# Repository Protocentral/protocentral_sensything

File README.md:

ProtoCentral Sensything
=======================================================

### Support us now on Crowd Supply at: https://www.crowdsupply.com/protocentral/sensything

Sensything is an ESP32-based IoT device that has multiple sensor interfaces to read from and send data from both analog and digital sensors.

## Information will be added constantly, keep checking this page for more.

License Information
===================

This product is open source! Both, our hardware and software are open source and licensed under the following licenses:

Hardware
---------

**All hardware is released under [Creative Commons Share-alike 4.0 International](http://creativecommons.org/licenses/by-sa/4.0/).**

You are free to:

* Share — copy and redistribute the material in any medium or format
* Adapt — remix, transform, and build upon the material for any purpose, even commercially.
The licensor cannot revoke these freedoms as long as you follow the license terms.

Under the following terms:

* Attribution — You must give appropriate credit, provide a link to the license, and indicate if changes were made. You may do so in any reasonable manner, but not in any way that suggests the licensor endorses you or your use.
* ShareAlike — If you remix, transform, or build upon the material, you must distribute your contributions under the same license as the original.

Software
--------

**All software is released under the MIT License(http://opensource.org/licenses/MIT).**

THE SOFTWARE IS PROVIDED "AS IS", WITHOUT WARRANTY OF ANY KIND, EXPRESS OR IMPLIED, INCLUDING BUT NOT LIMITED TO THE WARRANTIES OF MERCHANTABILITY, FITNESS FOR A PARTICULAR PURPOSE AND NONINFRINGEMENT. IN NO EVENT SHALL THE AUTHORS OR COPYRIGHT HOLDERS BE LIABLE FOR ANY CLAIM, DAMAGES OR OTHER LIABILITY, WHETHER IN AN ACTION OF CONTRACT, TORT OR OTHERWISE, ARISING FROM, OUT OF OR IN CONNECTION WITH THE SOFTWARE OR THE USE OR OTHER DEALINGS IN THE SOFTWARE.

Please check [*LICENSE.md*](LICENSE.md) for detailed license descriptions.

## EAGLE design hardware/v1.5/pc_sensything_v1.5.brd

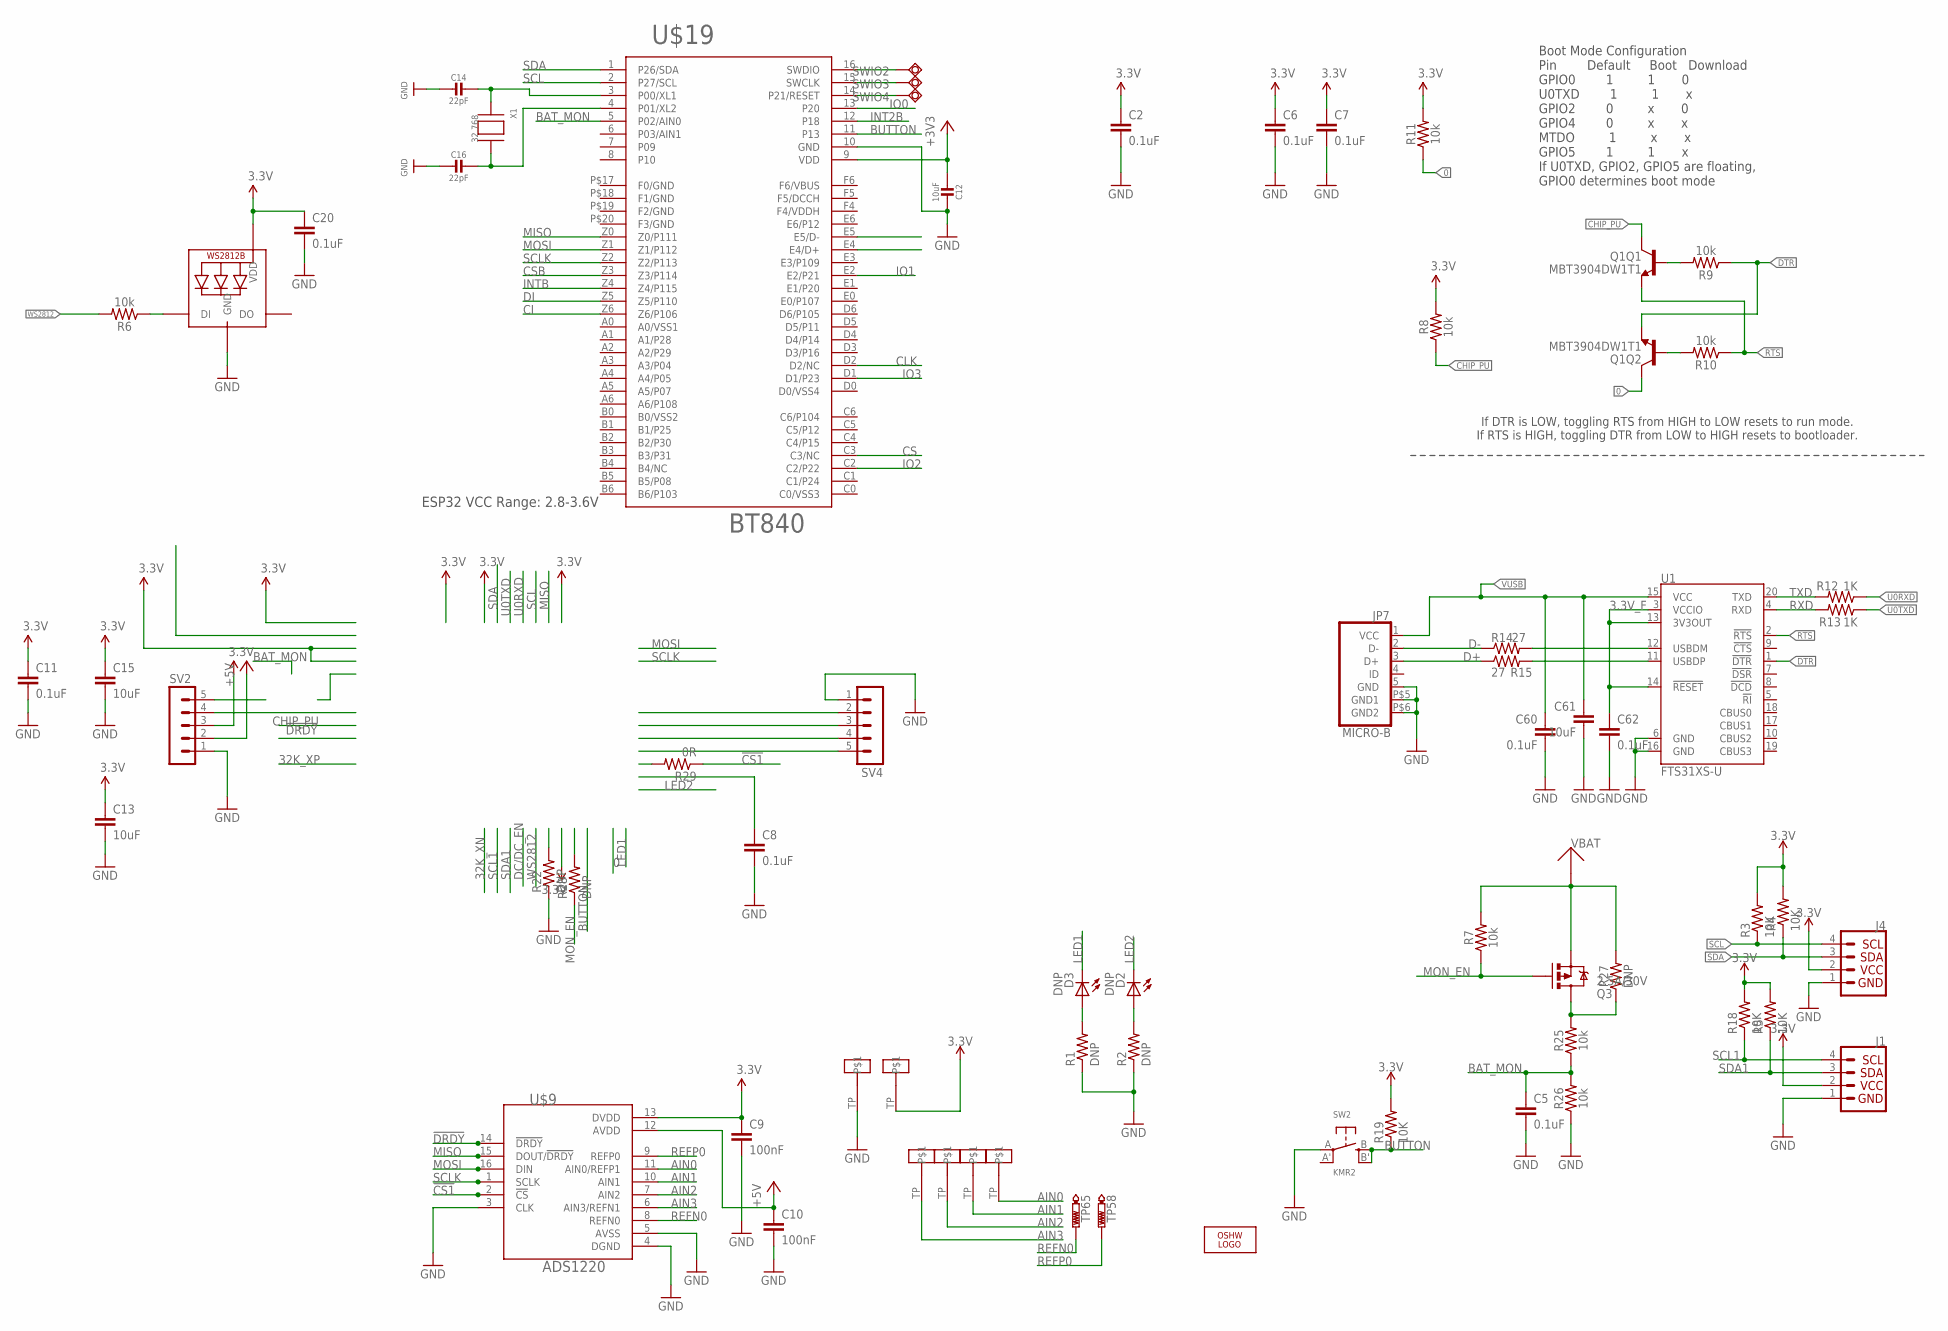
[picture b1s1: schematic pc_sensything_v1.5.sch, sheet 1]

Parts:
C2, C5, C6, C7, C8, C11: 0.1uF; 0402
C9, C10: 100nF; C0805
C12: 10uF; _0402
C13, C15: 10uF; 0603
C14, C16: 22pF; _0402
C20: 0.1uF; 0603
C60, C62: 0.1uF; C0402
C61: 10uF; C0805
D2, D3: DNP; CHIPLED_0603
J1, J4: QWIIC_CONNECTORJS-1MM; 1X04_1MM_RA
JP7: MICRO-B
LED1: WS2812B5050; WS2812B
LOGO3: OSHW_LOGO_FILLX0200-NT; OSHW_FILLX200_NOTEXT
Q1: MBT3904DW1T1; SC70-6
Q3: 2.5A/30V; SOT23-3
R1, R2, R22, R28: DNP; R0402
R3, R4, R5, R18, R19: 10K; R0402
R6, R7, R8, R9, R10, R11, R25, R26: 10k; 0603
R12, R13: 1K; R0402
R14, R15: 27; R0402
R27: DNP; 0603
R29: 0R; R0402
SV2, SV4: MA05-1
SW2: KMR2; BTN_KMR2_4.6X2.8
SWIO2, SWIO3, SWIO4: TPSQTP11R; TP11R
TP58, TP65: PTR1PAD1-13; P1-13
U1: FTS31XS-U; SSOP20_L
U$3, U$7, U$8, U$11, U$12, U$14: SENSYTHING_CON
U$9: ADS1220; TSSOP-16
U$19: BT840
X1: 32.768; XTAL3215

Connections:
0: Q1.6 (C), R11.1
3.3V: C2.1, C6.1, C7.1, C9.1, C11.1, C13.1, C15.1, C20.1, J1.2, J4.2, LED1.1-VDD (VDD), R3.2, R4.2, R5.2, R8.2, R11.2, R18.2, R19.2, SV2.3, U$9.13 (DVDD), U$14.TP; also elsewhere on the board
3.3V_F: C62.1, U1.3 (VCCIO), U1.13 (3V3OUT), U1.14 (!RESET)
!CS1: R29.1, U$9.2 (!CS)
!DRDY: U$9.14 (!DRDY)
+3V3: C12.1, U$19.9 (VDD)
+5V: C10.1, SV2.2, U$9.12 (AVDD); also elsewhere on the board
AIN0: U$9.11 (AIN0/REFP1), U$11.TP
AIN1: U$8.TP, U$9.10 (AIN1)
AIN2: U$7.TP, U$9.7 (AIN2)
AIN3: U$3.TP, U$9.6 (AIN3/REFN1)
BAT_MON: C5.1, R25.1, R26.2, U$19.5 (P02/AIN0)
BUTTON: R19.1, SW2.B (S), SW2.B' (S1), U$19.11 (P13)
CHIP_PU: Q1.3 (C), R8.1
CI: U$19.Z6 (Z6/P106)
CLK: U$19.D2 (D2/NC)
CS: U$19.C3 (C3/NC)
CSB: U$19.Z3 (Z3/P114)
D+: JP7.3 (D+), R15.1
D-: JP7.2 (D-), R14.1
DI: U$19.Z5 (Z5/P110)
DTR: Q1.1 (E), R9.1, U1.1 (!DTR)
GND: C2.2, C5.2, C6.2, C7.2, C8.2, C9.2, C10.2, C11.2, C12.2, C13.2, C14.2, C15.2, C16.2, C20.2, C60.2, C61.2, C62.2, J1.1, J4.1, JP7.5 (GND), JP7.P$5 (GND1), JP7.P$6 (GND2), LED1.3-GND (GND), R1.1, R2.1, R22.1, R26.1, SV2.1, SV4.1, SW2.A, U1.6 (GND), U1.16 (GND), U$9.3 (CLK), U$9.4 (DGND), U$9.5 (AVSS), U$12.TP, U$19.10 (GND); also elsewhere on the board
INT2B: U$19.12 (P18)
INTB: U$19.Z4 (Z4/P115)
IO0: U$19.13 (P20)
IO1: U$19.E2 (E2/P21)
IO2: U$19.C2 (C2/P22)
IO3: U$19.D1 (D1/P23)
LED1: D3.C
LED2: D2.C
MISO: U$9.15 (DOUT/!DRDY), U$19.Z0 (Z0/P111)
MON_EN: Q3.1 (G), R7.1, R28.1
MOSI: U$9.16 (DIN), U$19.Z1 (Z1/P112)
unnamed: D3.A, R1.2
unnamed: Q1.5 (B), R9.2
unnamed: D2.A, R2.2
unnamed: LED1.4-DIN (DI), R6.1
unnamed: Q1.2 (B), R10.2
unnamed: Q3.3 (D), R25.2, R27.1
unnamed: SWIO2.TP, U$19.16 (SWDIO)
unnamed: SWIO3.TP, U$19.15 (SWCLK)
unnamed: R14.2, U1.12 (USBDM)
unnamed: R15.2, U1.11 (USBDP)
unnamed: SWIO4.TP, U$19.14 (P21/RESET)
unnamed: C14.1, U$19.3 (P00/XL1), X1.P$1
unnamed: C16.1, U$19.4 (P01/XL2), X1.P$2
REFN0: TP65.TP, U$9.8 (REFN0)
REFP0: TP58.TP, U$9.9 (REFP0)
RTS: Q1.4 (E), R10.1, U1.2 (!RTS)
RXD: R13.2, U1.4 (RXD)
SCL: J4.4, R3.1, U$19.2 (P27/SCL)
SCL1: J1.4, R18.1
SCLK: U$9.1 (SCLK), U$19.Z2 (Z2/P113)
SDA: J4.3, R4.1, U$19.1 (P26/SDA)
SDA1: J1.3, R5.1
TXD: R12.2, U1.20 (TXD)
U0RXD: R12.1
U0TXD: R13.1
VBAT: Q3.2 (S), R7.2, R27.2; also elsewhere on the board
VUSB: C60.1, C61.1, JP7.1 (VCC), U1.15 (VCC); also elsewhere on the board
WS2812: R6.2

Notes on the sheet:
Boot Mode Configuration Pin Default Boot Download GPIO0 1 1 0 U0TXD 1 1 x GPIO2 0 x 0 GPIO4 0 x x MTDO 1 x x GPIO5 1 1 x If U0TXD, GPIO2, GPIO5 are floating, GPIO0 determines boot mode
ESP32 VCC Range: 2.8-3.6V
If DTR is LOW, toggling RTS from HIGH to LOW resets to run mode. If RTS is HIGH, toggling DTR from LOW to HIGH resets to bootloader.

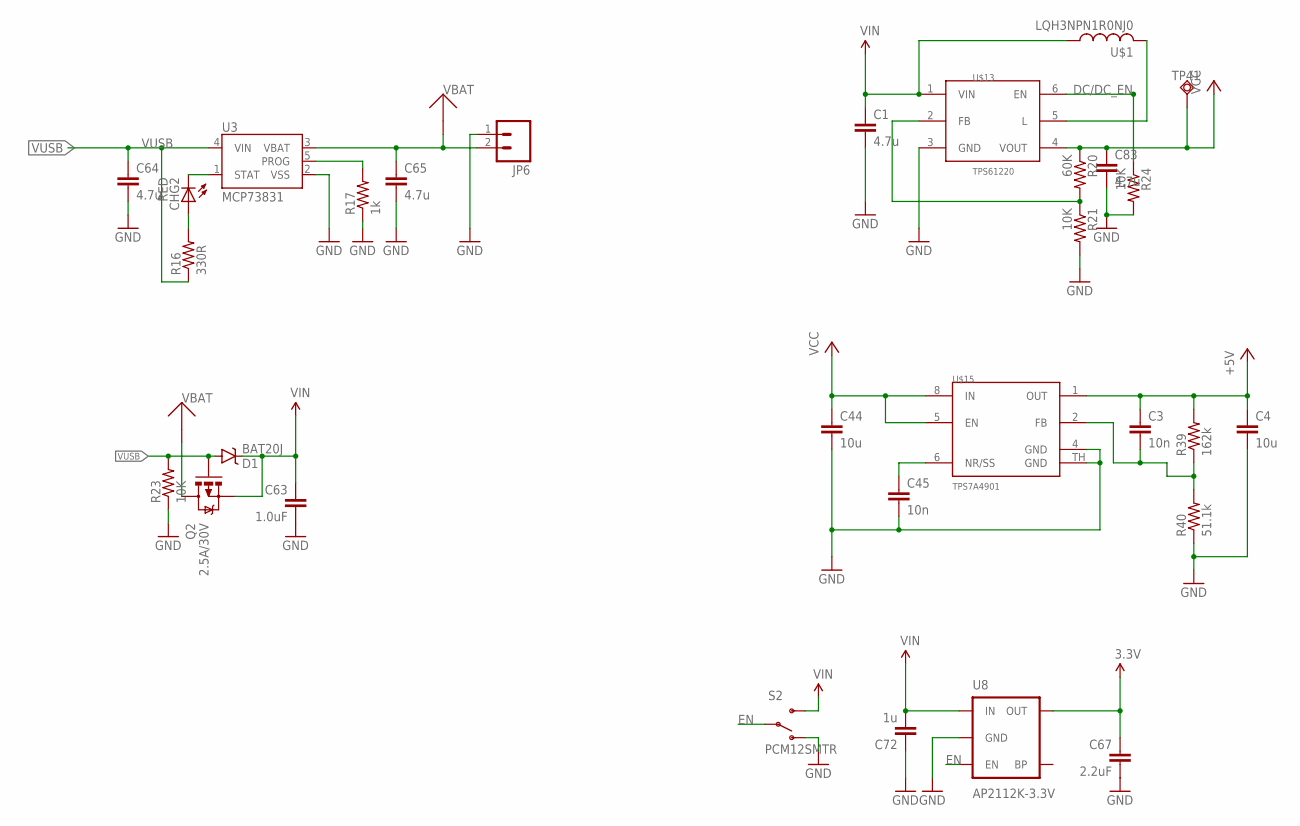
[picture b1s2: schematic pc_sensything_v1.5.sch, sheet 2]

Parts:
C1, C64, C65, C83: 4.7u; C0805
C3, C45: 10n; C0402
C4, C44: 10u; C0805
C63: 1.0uF; C0402
C67: 2.2uF; C0402
C72: 1u; C0402
CHG2: RED; CHIPLED_0603
D1: BAT20J; SOD-323
JP6: M02-JST-2MM-SMT; JST-2-SMD
Q2: 2.5A/30V; SOT23-3
R16: 330R; R0402
R17: 1k; R0402
R20: 60K; R0805
R21: 10K; R0805
R23, R24: 10K; R0402
R39: 162k; R0805
R40: 51.1k; R0805
S2: PCM12SMTR; SWITCH-SPST-SMD-A
TP41: TPSQB1,27; B1,27
U3: MCP73831; SOT23-5
U8: AP2112K-3.3V; SOT23-5
U$1: LQH3NPN1R0NJ0; LQH3NP
U$13: TPS61220; SC-70-6
U$15: TPS7A4901; S-PDSO-G08

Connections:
3.3V: C67.1, U8.5 (OUT); also elsewhere on the board
+5V: C3.1, C4.1, R39.2, U$15.1 (OUT); also elsewhere on the board
DC/DC_EN: R24.1, U$13.6 (EN)
EN: S2.2, U8.3 (EN)
GND: C1.2, C4.2, C44.2, C45.2, C63.2, C64.2, C65.2, C67.2, C72.1, C83.2, JP6.1, R17.1, R21.2, R23.1, R24.2, R40.1, S2.1 (O), U3.2 (VSS), U8.2 (GND), U$13.3 (GND), U$15.4 (GND), U$15.TH (GND); also elsewhere on the board
unnamed: CHG2.C, U3.1 (STAT)
unnamed: R20.2, R21.1, U$13.2 (FB)
unnamed: C45.1, U$15.6 (NR/SS)
unnamed: C3.2, R39.1, R40.2, U$15.2 (FB)
unnamed: CHG2.A, R16.2
unnamed: R17.2, U3.5 (PROG)
unnamed: U$1.P$2 (2), U$13.5 (L)
VBAT: C65.1, JP6.2, Q2.3 (D), U3.3 (VBAT); also elsewhere on the board
VCC: C44.1, C83.1, R20.1, TP41.TP, U$13.4 (VOUT), U$15.5 (EN), U$15.8 (IN)
VIN: C1.1, C63.1, C72.2, D1.C, Q2.2 (S), S2.3 (S), U8.1 (IN), U$1.P$1 (1), U$13.1 (VIN)
VUSB: C64.1, D1.A, Q2.1 (G), R16.1, R23.2, U3.4 (VIN); also elsewhere on the board

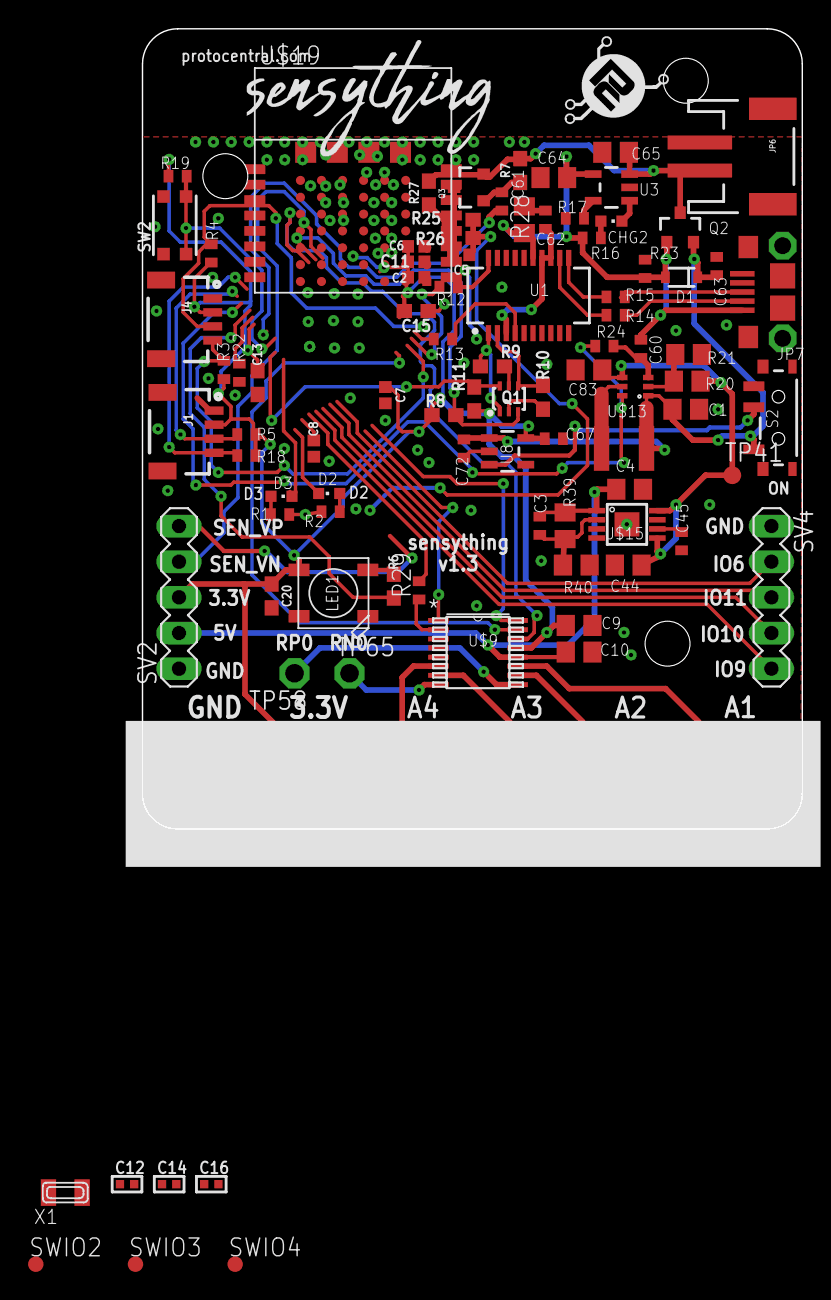
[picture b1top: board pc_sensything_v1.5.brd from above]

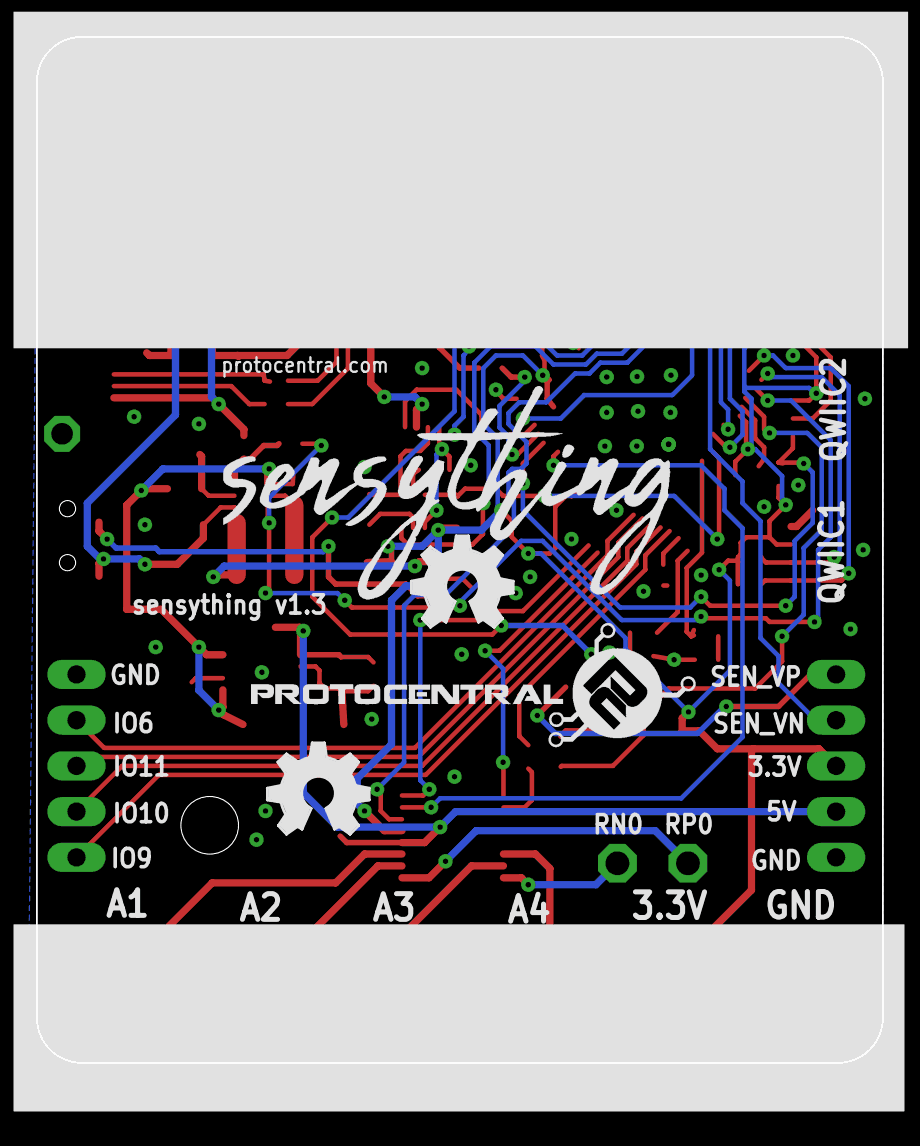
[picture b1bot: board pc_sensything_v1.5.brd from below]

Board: 4 copper layers, 47.0 x 57.0 mm, 102 parts (4 on the bottom side), 56 nets.

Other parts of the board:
LOGO2: OSHW_LOGO_FILLX0200-NT; OSHW_FILLX200_NOTEXT
U$2: SENSYTHING
U$4: SENSYTHING_SMALL
U$6: LOGO-PROTY
U$26: PROTY_LOGO_WITH_TEXT; PROTY_WITH_TEXT@1

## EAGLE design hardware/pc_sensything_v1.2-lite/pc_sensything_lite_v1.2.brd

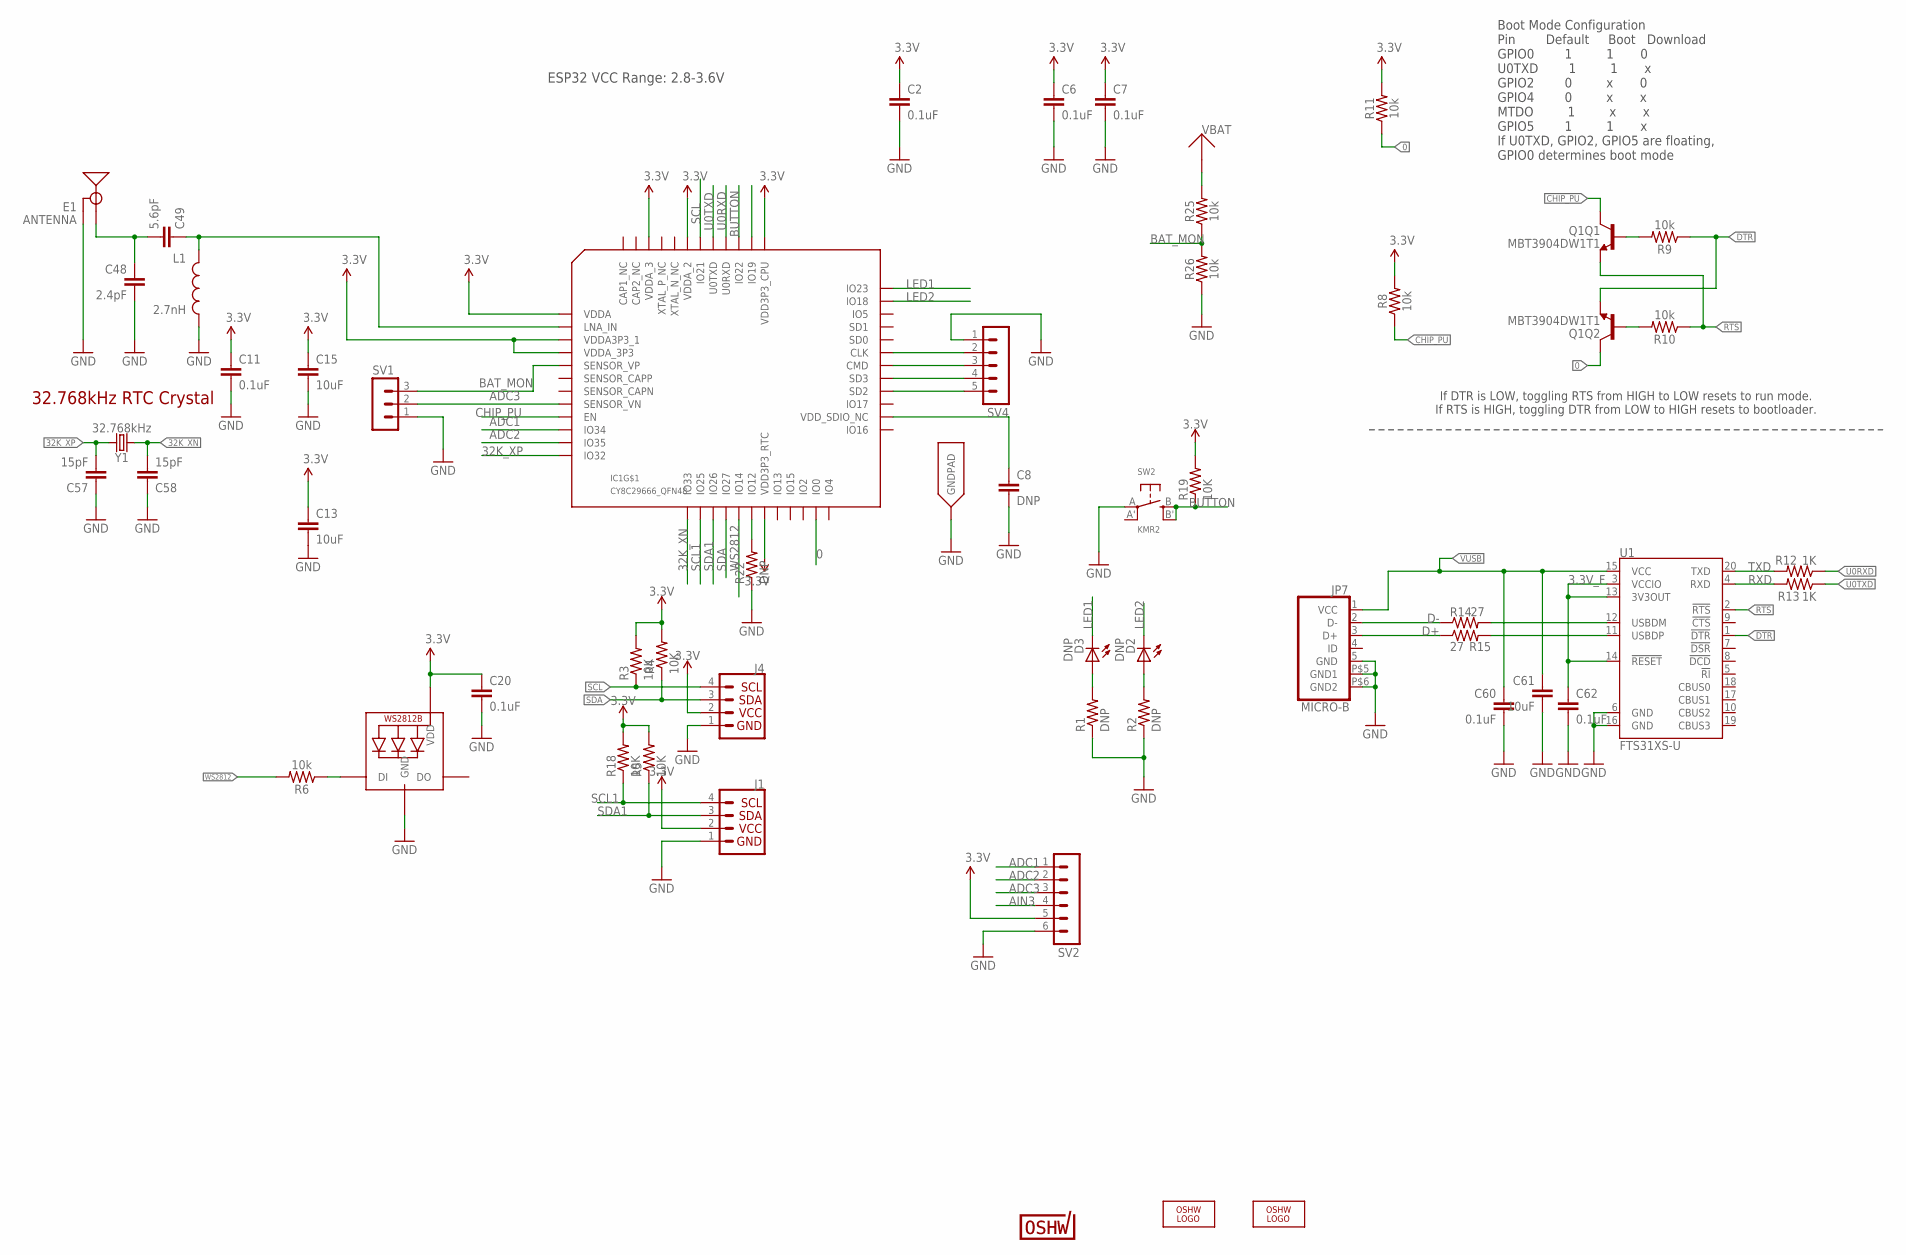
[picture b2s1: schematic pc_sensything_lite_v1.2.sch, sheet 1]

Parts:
C2, C6, C7, C11: 0.1uF; 0402
C8: DNP; 0603
C13: 10uF; C0402
C15: 10uF; 0603
C20: 0.1uF; 0603
C48: 2.4pF; 0603
C49: 5.6pF; 0603
C57, C58: 15pF; 0603
C60, C62: 0.1uF; C0402
C61: 10uF; C0805
D2, D3: DNP; CHIPLED_0603
E1: ANTENNA; TRACE_ANTENNA_2.4GHZ_25.7MM_TUNED
IC1: CY8C29666_QFN48; QFN48
J1, J4: QWIIC_CONNECTORJS-1MM; 1X04_1MM_RA
JP7: MICRO-B
L1: 2.7nH; 0603
LED1: WS2812B5050; WS2812B
LOGO1, LOGO3: OSHW_LOGO_FILLX0200-NT; OSHW_FILLX200_NOTEXT
Q1: MBT3904DW1T1; SC70-6
R1, R2, R22: DNP; R0402
R3, R4, R5, R18, R19: 10K; R0402
R6, R8, R9, R10, R11, R25, R26: 10k; 0603
R12, R13: 1K; R0402
R14, R15: 27; R0402
SV1: MA03-1
SV2: MA06-1
SV4: MA05-1
SW2: KMR2; BTN_KMR2_4.6X2.8
U1: FTS31XS-U; SSOP20_L
U$22: CERT-SMALL; CERT-SMALL-SILK
Y1: 32.768kHz; CRYSTAL-SMD-3.2X1.5MM

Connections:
0: IC1.23 (IO0), Q1.6 (C), R11.1
3.3V: C2.1, C6.1, C7.1, C11.1, C13.1, C15.1, C20.1, IC1.1 (VDDA), IC1.3 (VDDA3P3_1), IC1.4 (VDDA_3P3), IC1.19 (VDD3P3_RTC), IC1.37 (VDD3P3_CPU), IC1.43 (VDDA_2), IC1.46 (VDDA_3), J1.2, J4.2, LED1.1-VDD (VDD), R3.2, R4.2, R5.2, R8.2, R11.2, R18.2, R19.2, SV2.5; also elsewhere on the board
3.3V_F: C62.1, U1.3 (VCCIO), U1.13 (3V3OUT), U1.14 (!RESET)
32K_XN: C58.2, IC1.13 (IO33), Y1.P$2 (2)
32K_XP: C57.2, IC1.12 (IO32), Y1.P$1 (1)
ADC1: IC1.10 (IO34), SV2.1
ADC2: IC1.11 (IO35), SV2.2
ADC3: IC1.8 (SENSOR_VN), SV1.2, SV2.3
AIN3: SV2.4
BAT_MON: IC1.5 (SENSOR_VP), R25.1, R26.2, SV1.3
BUTTON: IC1.39 (IO22), R19.1, SW2.B (S), SW2.B' (S1)
CHIP_PU: IC1.9 (EN), Q1.3 (C), R8.1
D+: JP7.3 (D+), R15.1
D-: JP7.2 (D-), R14.1
DTR: Q1.1 (E), R9.1, U1.1 (!DTR)
GND: C2.2, C6.2, C7.2, C8.2, C11.2, C13.2, C15.2, C20.2, C48.2, C57.1, C58.1, C60.2, C61.2, C62.2, E1.GND, E1.GND2 (GND), IC1.EXP (GNDPAD), J1.1, J4.1, JP7.5 (GND), JP7.P$5 (GND1), JP7.P$6 (GND2), L1.2, LED1.3-GND (GND), R1.1, R2.1, R22.1, R26.1, SV1.1, SV2.6, SV4.1, SW2.A, U1.6 (GND), U1.16 (GND); also elsewhere on the board
LED1: D3.C, IC1.36 (IO23)
LED2: D2.C, IC1.35 (IO18)
LNA_IN: C49.1, IC1.2 (LNA_IN), L1.1
unnamed: C8.1, IC1.26 (VDD_SDIO_NC)
unnamed: IC1.18 (IO12), R22.2
unnamed: D3.A, R1.2
unnamed: Q1.5 (B), R9.2
unnamed: D2.A, R2.2
unnamed: LED1.4-DIN (DI), R6.1
unnamed: Q1.2 (B), R10.2
unnamed: IC1.28 (SD2), SV4.5
unnamed: IC1.29 (SD3), SV4.4
unnamed: IC1.30 (CMD), SV4.3
unnamed: IC1.31 (CLK), SV4.2
unnamed: R14.2, U1.12 (USBDM)
unnamed: R15.2, U1.11 (USBDP)
RTS: Q1.4 (E), R10.1, U1.2 (!RTS)
RXD: R13.2, U1.4 (RXD)
SCL: IC1.42 (IO21), J4.4, R3.1
SCL1: IC1.14 (IO25), J1.4, R18.1
SDA: IC1.16 (IO27), J4.3, R4.1
SDA1: IC1.15 (IO26), J1.3, R5.1
SENSOR_CAPN: IC1.7 (SENSOR_CAPN)
TRACE_ANT2: C48.1, C49.2, E1.ANT (SIGNAL)
TXD: R12.2, U1.20 (TXD)
U0RXD: IC1.40 (U0RXD), R12.1
U0TXD: IC1.41 (U0TXD), R13.1
VBAT: R25.2; also elsewhere on the board
VUSB: C60.1, C61.1, JP7.1 (VCC), U1.15 (VCC); also elsewhere on the board
WS2812: IC1.17 (IO14), R6.2

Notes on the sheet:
Boot Mode Configuration Pin Default Boot Download GPIO0 1 1 0 U0TXD 1 1 x GPIO2 0 x 0 GPIO4 0 x x MTDO 1 x x GPIO5 1 1 x If U0TXD, GPIO2, GPIO5 are floating, GPIO0 determines boot mode
32.768kHz RTC Crystal
ESP32 VCC Range: 2.8-3.6V
If DTR is LOW, toggling RTS from HIGH to LOW resets to run mode. If RTS is HIGH, toggling DTR from LOW to HIGH resets to bootloader.

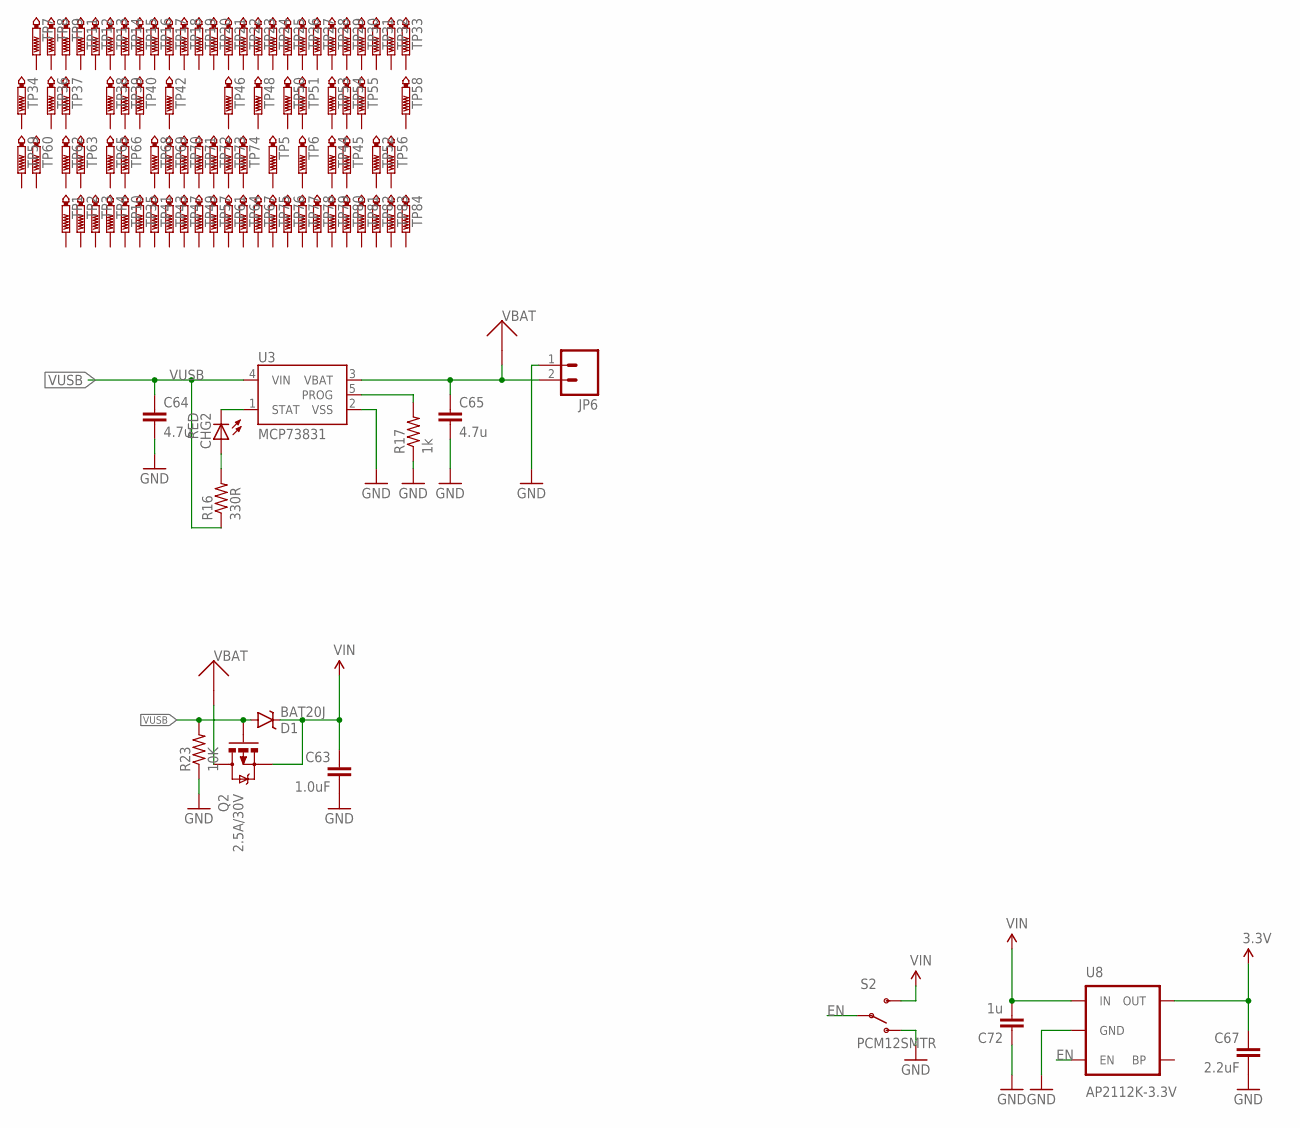
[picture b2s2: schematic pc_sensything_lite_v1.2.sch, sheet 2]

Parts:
C63: 1.0uF; C0402
C64, C65: 4.7u; C0805
C67: 2.2uF; C0402
C72: 1u; C0402
CHG2: RED; CHIPLED_0603
D1: BAT20J; SOD-323
JP6: M02-JST-2MM-SMT; JST-2-SMD
Q2: 2.5A/30V; SOT23-3
R16: 330R; R0402
R17: 1k; R0402
R23: 10K; R0402
S2: PCM12SMTR; SWITCH-SPST-SMD-A
TP1, TP2, TP3, TP4, TP5, TP6, TP7, TP8, TP9, TP10, TP11, TP12, TP13, TP14, TP15, TP16, TP17, TP18, TP19, TP20, TP21, TP22, TP23, TP24, TP25, TP26, TP27, TP28, TP29, TP30, TP31, TP32, TP33, TP34, TP35, TP36, TP37, TP38, TP39, TP40, TP41, TP42, TP43, TP44, TP45, TP46, TP47, TP48, TP49, TP50, TP51, TP52, TP53, TP54, TP55, TP56, TP57, TP58, TP59, TP60, TP61, TP62, TP63, TP64, TP65, TP66, TP67, TP68, TP69, TP70, TP71, TP72, TP73, TP74, TP75, TP76, TP77, TP78, TP79, TP80, TP81, TP82, TP83, TP84: PTR1PAD1-13; P1-13
U3: MCP73831; SOT23-5
U8: AP2112K-3.3V; SOT23-5

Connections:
3.3V: C67.1, U8.5 (OUT); also elsewhere on the board
EN: S2.2, U8.3 (EN)
GND: C63.2, C64.2, C65.2, C67.2, C72.1, JP6.1, R17.1, R23.1, S2.1 (O), U3.2 (VSS), U8.2 (GND); also elsewhere on the board
unnamed: CHG2.C, U3.1 (STAT)
unnamed: CHG2.A, R16.2
unnamed: R17.2, U3.5 (PROG)
VBAT: C65.1, JP6.2, Q2.3 (D), U3.3 (VBAT); also elsewhere on the board
VIN: C63.1, C72.2, D1.C, Q2.2 (S), S2.3 (S), U8.1 (IN)
VUSB: C64.1, D1.A, Q2.1 (G), R16.1, R23.2, U3.4 (VIN); also elsewhere on the board

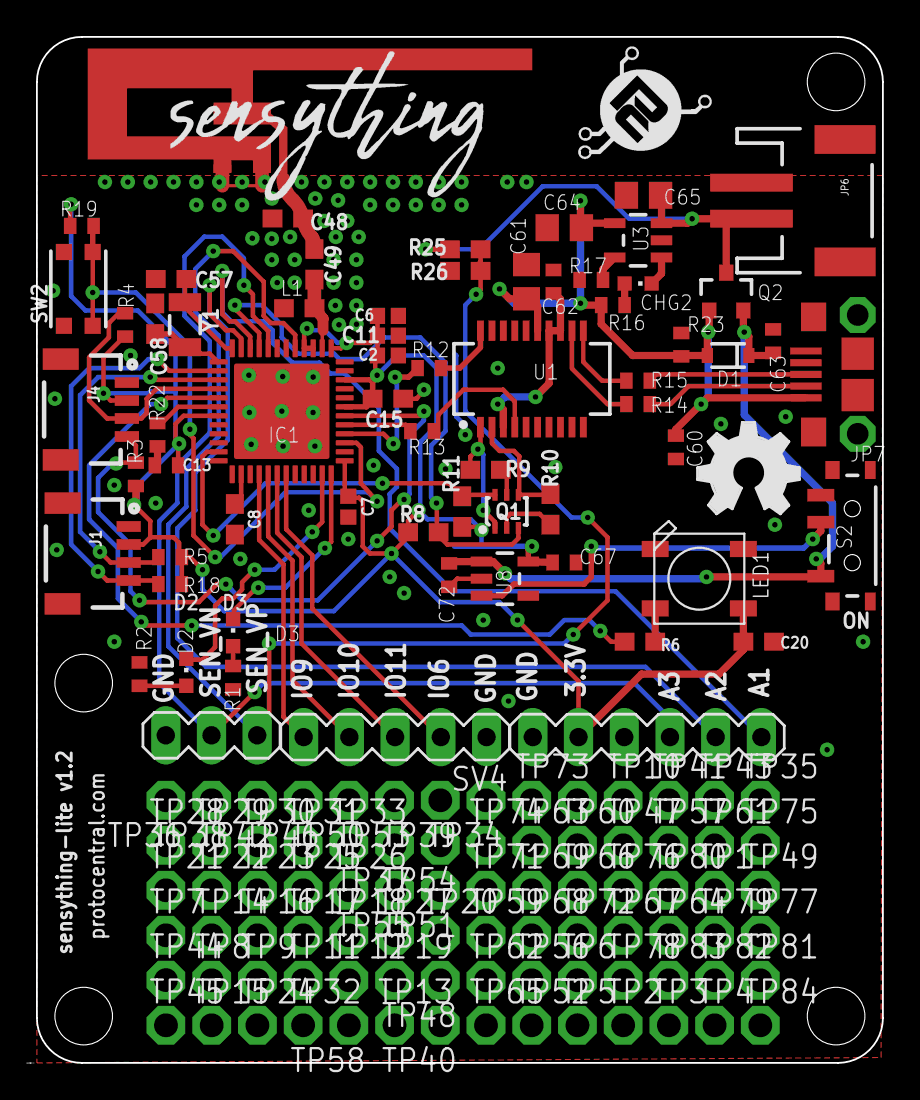
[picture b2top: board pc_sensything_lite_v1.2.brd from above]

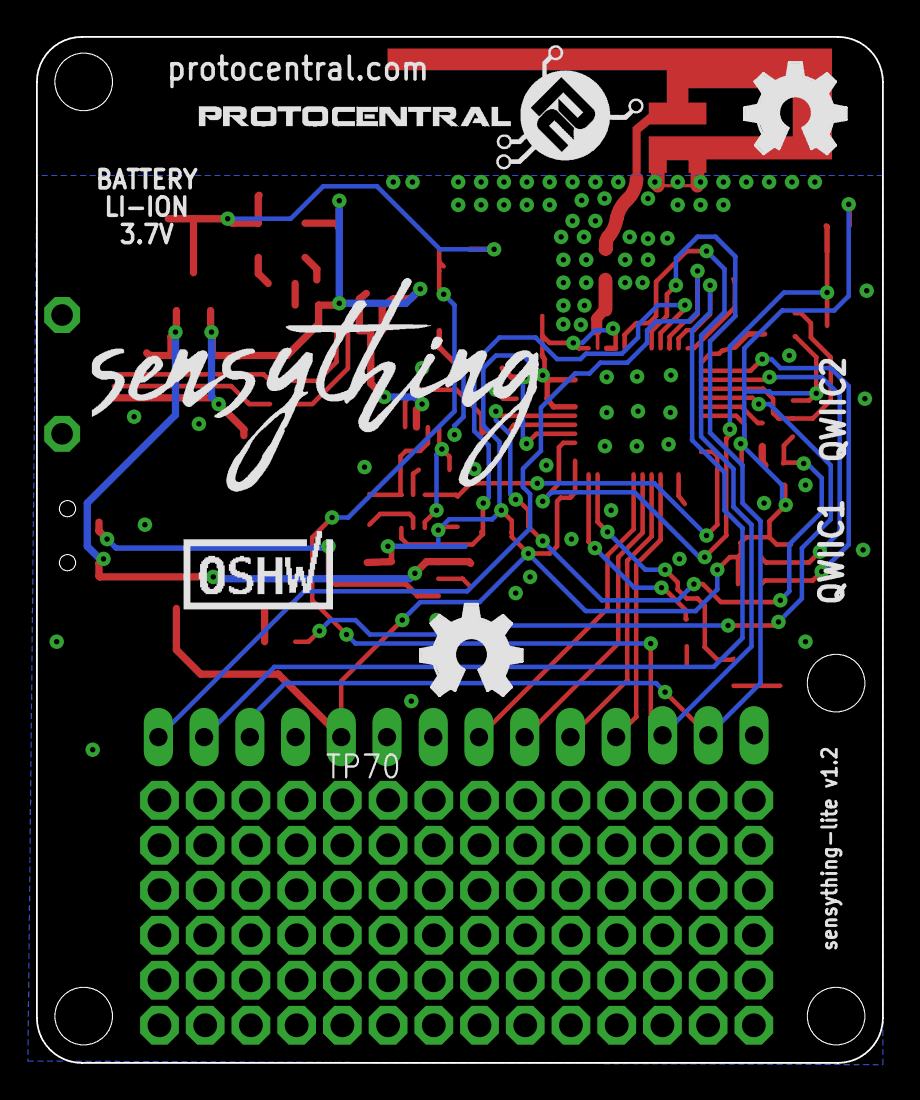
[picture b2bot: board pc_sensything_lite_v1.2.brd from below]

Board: 4 copper layers, 47.0 x 57.0 mm, 157 parts (6 on the bottom side), 49 nets.

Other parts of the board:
LOGO2: OSHW_LOGO_FILLX0200-NT; OSHW_FILLX200_NOTEXT
U$2: SENSYTHING
U$4: SENSYTHING_SMALL
U$6: LOGO-PROTY
U$26: PROTY_LOGO_WITH_TEXT; PROTY_WITH_TEXT@1

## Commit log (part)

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2019-01-09 Added code for Sensything
2019-01-09 Rename sensything-with-arduino.md to Beginner.md
2019-01-09 Updated docs theme
2019-01-09 Updated config
2019-01-09 Minor formatting
2019-01-09 More minor format fixes
2019-01-09 Removed unwated
2019-01-09 Restructured docs
2019-01-09 Updated menu
2019-01-09 corrections
2019-01-09 Docs
2019-01-09 renamed
2019-01-09 Formatting
2019-01-09 YAML
2019-01-09 Reorganize
2019-01-09 Added new docs
2019-01-10 Create Sensything with BLE
2019-01-10 Rename Sensything with BLE to Sensything with BLE.md
2019-01-10 Added index
2019-01-10 Minor formatting fix
2019-01-12 Updated content
2019-01-16 Added Sensything code
2019-01-22 Added Sensything BLE with Arduino
2019-02-17 added accelerometer code
2019-02-19 Added Sensything Arduino Ble
2019-03-01 added activity classifier with sensything
2019-03-01 added activity classifier with webserver

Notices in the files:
README.md:
CC-BY-SA-4.0
parts and their libraries:
SparkFun-Capacitors: Licensing: Creative Commons ShareAlike 4.0 International - https://creativecommons.org/licenses/by-sa/4.0
SparkFun-DigitalIC: Licensing: CC v3.0 Share-Alike You are welcome to use this library for commercial purposes.
